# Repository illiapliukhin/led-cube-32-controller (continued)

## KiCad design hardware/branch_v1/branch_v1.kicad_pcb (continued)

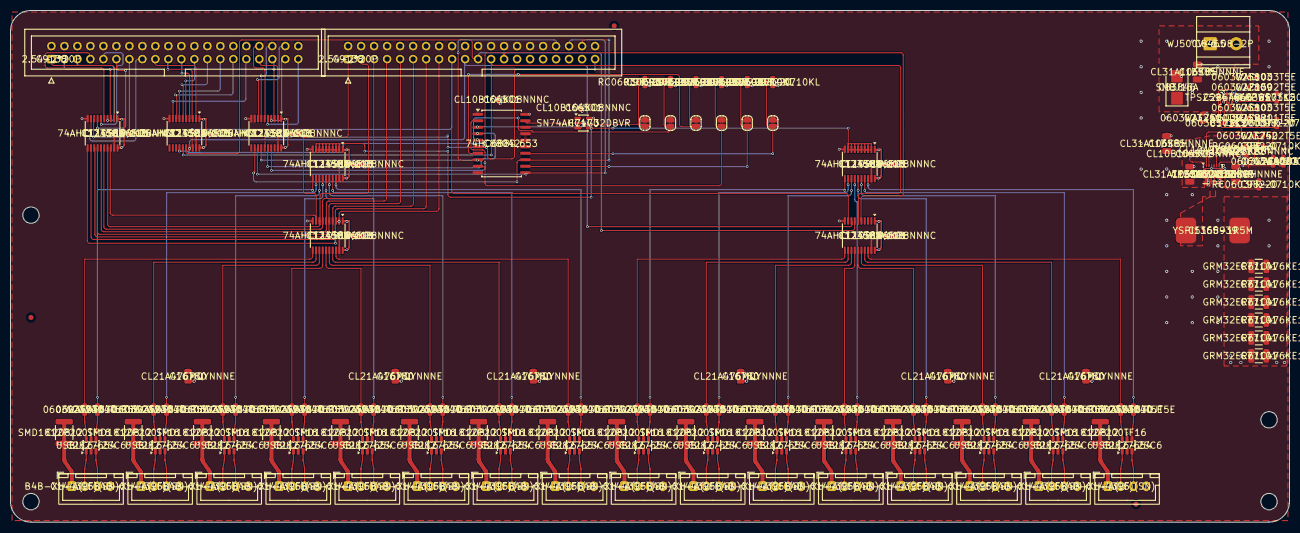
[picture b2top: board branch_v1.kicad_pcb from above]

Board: 2 copper layers, 250.0 x 100.0 mm, 156 parts (0 on the bottom side), 151 nets.

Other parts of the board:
FID1, FID2, FID3: FID; Fiducial_1mm_Mask2mm
H1, H2, H3, H4: M3; MountingHole_3.2mm_M3

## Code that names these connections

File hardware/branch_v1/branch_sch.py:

#!/usr/bin/env python3
"""Branch (strand) board v1 schematic: 16 HD108/SK9822 strands, clock-gated by board ID."""
import sys,os
HERE=os.path.dirname(os.path.abspath(__file__)); sys.path.insert(0,os.path.join(HERE,'../../tools'))
from schgen import write, PINNAMES
BUS=['D%d'%i for i in range(16)]+['CLK','A0','A1','A2','A3','A4','A5']
def portpin(sig):
    if sig.startswith('D'): return 1+2*int(sig[1:])
    return {'CLK':33,'A0':35,'A1':37,'A2':39,'A3':34,'A4':36,'A5':38}[sig]
C=[]
def comp(ref,val,fp,pins,lcsc='',mpn=''):
    C.append(dict(ref=ref,value=val,footprint=fp,fields={'LCSC':lcsc,'MPN':mpn},pins=pins))
for J,pre in (('J1','IN_'),('J2','L_')):
    m={portpin(s):pre+s for s in BUS}
    comp(J,'BUS_%s 2x20'%('IN' if J=='J1' else 'OUT'),'Connector_IDC:IDC-Header_2x20_P2.54mm_Vertical',
         [(str(n),m.get(n,'GND').replace(pre,'') if n in m else 'GND',m.get(n,'GND')) for n in range(1,41)],'C9138','2.54-2*20P')
G=[BUS[0:8],BUS[8:16],['CLK','A0','A1','A2','A3','A4','A5',None]]
pn=PINNAMES['74AHCT245PW']
def buf(ref,ins,outs):
    pins=[]
    for n in range(1,21):
        s=str(n); name=pn[s]
        if n==1: net='+5V'
        elif n==10: net='GND'
        elif n==19: net='GND'
        elif n==20: net='+5V'
        elif 2<=n<=9: net=ins[n-2]
        else: net=outs[18-n]
        pins.append((s,name,net))
    comp(ref,'74AHCT245PW','Package_SO:TSSOP-20_4.4x6.5mm_P0.65mm',pins,'C173388','74AHCT245PW,118')
for i,g in enumerate(G):
    buf('U%d'%(i+1),[('IN_'+s if s else 'GND') for s in g],[('L_'+s if s else None) for s in g])
# comparator
cmp_pins=[('1','~G','GND'),('10','GND','GND'),('20','VCC','+5V'),('19','~P=Q','SEL_N')]
for k,(pp,qp) in enumerate([(2,3),(4,5),(6,7),(8,9),(11,12),(13,14),(15,16),(17,18)]):
    cmp_pins+= [(str(pp),'P%d'%k,'L_A%d'%k if k<6 else 'GND'),(str(qp),'Q%d'%k,'ID%d'%k if k<6 else 'GND')]
comp('U4','74HC688D','Package_SO:SOIC-20W_7.5x12.8mm_P1.27mm',sorted(cmp_pins,key=lambda p:int(p[0])),'C88042','74HC688D,653')
comp('U5','SN74AHC1G32DBVR','Package_TO_SOT_SMD:SOT-23-5',[('1','A','L_CLK'),('2','B','SEL_N'),('3','GND','GND'),('4','Y','GCLK'),('5','VCC','+5V')],'C7470','SN74AHC1G32DBVR')
buf('U6',['L_D%d'%i for i in range(7,-1,-1)],['SDR%d'%i for i in range(7,-1,-1)])   # reversed: matches left-to-right fan-out
buf('U7',['L_D%d'%i for i in range(15,7,-1)],['SDR%d'%i for i in range(15,7,-1)])
buf('U8',['GCLK']*8,['SCR%d'%i for i in range(7,-1,-1)])
buf('U9',['GCLK']*8,['SCR%d'%i for i in range(15,7,-1)])
for i in range(16):
    comp('RD%d'%i,'33R','Resistor_SMD:R_0603_1608Metric',[('1','1','SDR%d'%i),('2','2','SD%d'%i)],'C23140','0603WAF330JT5E')
    comp('RC%d'%i,'33R','Resistor_SMD:R_0603_1608Metric',[('1','1','SCR%d'%i),('2','2','SC%d'%i)],'C23140','0603WAF330JT5E')
    comp('J%d'%(10+i),'STRAND%d'%i,'Connector_JST:JST_XH_B4B-XH-A_1x04_P2.50mm_Vertical',[('1','+5V','V5S%d'%i),('2','DATA','SD%d'%i),('3','CLK','SC%d'%i),('4','GND','GND')],'C144395','B4B-XH-A(LF)(SN)')
    # per-output fuse (2 A hold PTC) and ESD clamp on the 1 m strand lines (lesson: fuse per output, ESD at connector)
    comp('F%d'%(10+i),'PTC 2A','Fuse:Fuse_1812_4532Metric',[('1','1','+5V'),('2','2','V5S%d'%i)],'C20812','SMD1812P200TF16')
    comp('UE%d'%i,'USBLC6-2SC6','Package_TO_SOT_SMD:SOT-23-6',[('1','IO1','SD%d'%i),('6','IO1b','SD%d'%i),('3','IO2','SC%d'%i),('4','IO2b','SC%d'%i),('2','GND','GND'),('5','VBUS','+5V')],'C2827654','USBLC6-2SC6')
for k in range(6):
    comp('RID%d'%k,'10k','Resistor_SMD:R_0603_1608Metric',[('1','1','+5V'),('2','2','ID%d'%k)],'C98220','RC0603FR-0710KL')
    comp('JP%d'%k,'ID%d_SET'%k,'Jumper:SolderJumper-2_P1.3mm_Open_RoundedPad1.0x1.5mm',[('1','1','ID%d'%k),('2','2','GND')])
for i in range(1,10):
    comp('C%d'%i,'100nF','Capacitor_SMD:C_0603_1608Metric',[('1','1','+5V'),('2','2','GND')],'C66501','CL10B104KO8NNNC')
for i in range(10,16):
    comp('C%d'%i,'47uF','Capacitor_SMD:C_0805_2012Metric',[('1','1','+5V'),('2','2','GND')],'C16780','CL21A476MQYNNNE')
# ---- 12 V input -> TVS -> eFuse (rev-polarity, 4.46 A limit) -> 12 A sync buck -> +5V (local injection) ----
for j in ('J30',):   # 12 V drop from the trunk (trunk is spliced in the cable, not passed through the PCB)
    comp(j,'12V_BUS','TerminalBlock_Phoenix:TerminalBlock_Phoenix_MKDS-1,5-2-5.08_1x02_P5.08mm_Horizontal',[('1','+12V','V12_IN'),('2','GND','GND')],'C8465','WJ500V-5.08-2P')
comp('D30','SMBJ15A','Diode_SMD:D_SMB',[('1','K','V12_IN'),('2','A','GND')],'C83846','SMBJ15A')
comp('U30','TPS259474LRPWR','cube:TI_RPW0010A_VQFN-HR-10_2x2mm_P0.45mm',[('1','EN/UVLO','EFEN'),('2','OVLO','EFOV'),('3','PG','PG12'),('4','PGTH','EFEN'),('5','IN','V12_IN'),('6','OUT','+12V'),('7','DVDT','DVDT'),('8','GND','GND'),('9','ILM','ILM'),('10','ITIMER','ITMR')],'C2864845','TPS259474LRPWR')
for ref,val,a_,b_,c_,m_ in (('R30','100k','V12_IN','EFEN','C25803','0603WAF1003T5E'),('R31','15k','EFEN','GND','C22809','0603WAF1502T5E'),   # UVLO = 1.2*(1+100/15) = 9.2 V
                            ('R40','100k','V12_IN','EFOV','C25803','0603WAF1003T5E'),('R32','8.2k','EFOV','GND','C25981','0603WAF8201T5E'),('R33','750R','ILM','GND','C23241','0603WAF7500T5E'),('R34','10k','PG12','+5V','C98220','RC0603FR-0710KL')):
    comp(ref,val,'Resistor_SMD:R_0603_1608Metric',[('1','1',a_),('2','2',b_)],c_,m_)
comp('C30','10nF','Capacitor_SMD:C_0603_1608Metric',[('1','1','DVDT'),('2','2','GND')],'C57112','0603B103K500NT')
comp('C31','10nF','Capacitor_SMD:C_0603_1608Metric',[('1','1','ITMR'),('2','2','GND')],'C57112','0603B103K500NT')
for k in range(32,36):
    comp('C%d'%k,'10uF/50V','Capacitor_SMD:C_1206_3216Metric',[('1','1','+12V' if k>32 else 'V12_IN'),('2','2','GND')],'C13585','CL31A106KBHNNNE')
comp('U31','TPS56C215RNNR','Package_DFN_QFN:Texas_RNN0018A',[('1','BOOT','BST'),('2','VIN','+12V'),('11','VIN_2','+12V'),('3','PGND','GND'),('4','PGND_2','GND'),('5','PGND_3','GND'),('8','PGND_4','GND'),('9','PGND_5','GND'),('10','PGND_6','GND'),
    ('6','SW','SW5'),('7','SW_2','SW5'),('12','AGND','GND'),('13','FB','FB5'),('14','SS','SS5'),('15','EN','+12V'),('16','PGOOD','PG5'),('17','VREG5','VREG5'),('18','MODE','MODE5')],'C473372','TPS56C215RNNR')
comp('L30','1.5uH 20A','cube:L_YJYCOIN_YSPI1365',[('1','1','SW5'),('2','2','+5V')],'C5158939','YSPI1365-1R5M')
comp('C36','100nF','Capacitor_SMD:C_0603_1608Metric',[('1','1','BST'),('2','2','SW5')],'C66501','CL10B104KO8NNNC')
comp('C37','4.7uF','Capacitor_SMD:C_0603_1608Metric',[('1','1','VREG5'),('2','2','GND')],'C19666','CL10A475KO8NNNC')
comp('C38','22nF','Capacitor_SMD:C_0603_1608Metric',[('1','1','SS5'),('2','2','GND')],'C21122','CL10B223KB8NNNC')
for ref,val,a_,b_,c_,m_ in (('R35','75k','+5V','FB5','C23242','0603WAF7502T5E'),('R36','10k','FB5','GND','C98220','RC0603FR-0710KL'),
                            ('R37','120k','VREG5','MODE5','C25808','0603WAF1203T5E'),('R38','20k','MODE5','GND','C4184','0603WAF2002T5E'),('R39','10k','PG5','+5V','C98220','RC0603FR-0710KL')):
    comp(ref,val,'Resistor_SMD:R_0603_1608Metric',[('1','1',a_),('2','2',b_)],c_,m_)
for k in range(40,46):
    comp('C%d'%k,'47uF/16V','Capacitor_SMD:C_1210_3225Metric',[('1','1','+5V'),('2','2','GND')],'C77101','GRM32ER61C476KE15L')
n=write(os.path.join(HERE,'branch_v1.kicad_sch'),C,'Branch board v1 - 16 clocked RGB strands','branch_v1')
open(os.path.join(HERE,'branch_v1.kicad_pro'),'w').write('{"meta":{"filename":"branch_v1.kicad_pro","version":1}}')
print('components',n)
